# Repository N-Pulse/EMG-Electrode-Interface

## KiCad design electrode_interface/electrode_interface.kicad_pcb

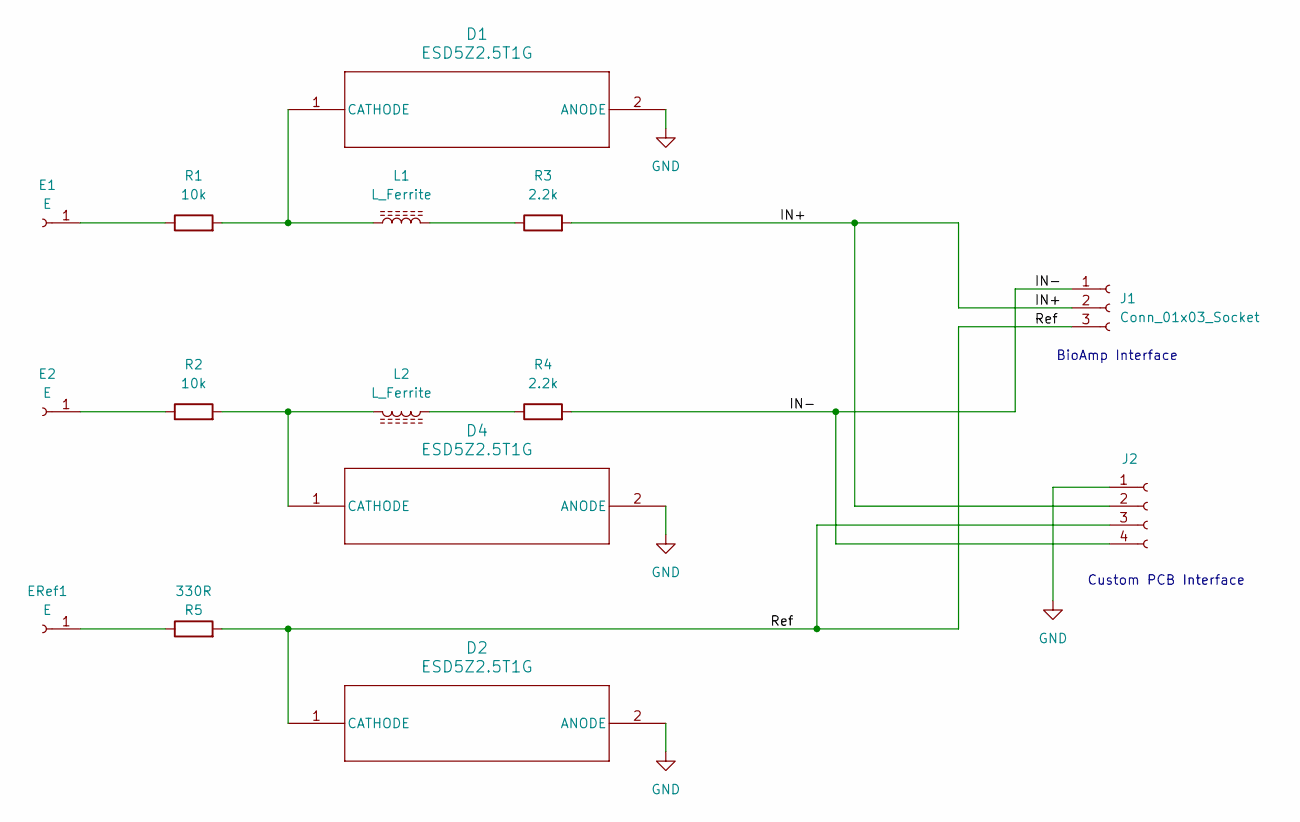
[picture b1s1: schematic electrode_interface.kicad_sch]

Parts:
D1, D2, D4: ESD5Z2.5T1G; SOD-523_0P9X1P3_ONS
E1, E2: E; ElectrodeHolder
ERef1: E; ElectrodeHolder
J1: Conn_01x03_Socket; PinHeader_1x03_P2.54mm_Vertical
J2: Conn_01x04_Socket; PinSocket_2x02_P2.54mm_Vertical
L1, L2: L_Ferrite; IND_BLM15_1P05X0P55X0P55_MUR
R1, R2: 10k; R_0402_1005Metric
R3, R4: 2.2k; R_0402_1005Metric
R5: 330R; R_0402_1005Metric

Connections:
/IN+: J1.2, J2.2, R3.2
/IN-: J1.1, J2.4, R4.2
/Ref: D2.1 (CATHODE), J1.3, J2.3, R5.2
GND: D1.2 (ANODE), D2.2 (ANODE), D4.2 (ANODE), J2.1
unnamed: D1.1 (CATHODE), L1.1, R1.2
unnamed: D4.1 (CATHODE), L2.2, R2.2
unnamed: E1.1, R1.1
unnamed: E2.1, R2.1
unnamed: ERef1.1, R5.1
unnamed: L1.2, R3.1
unnamed: L2.1, R4.1

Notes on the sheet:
BioAmp Interface
Custom PCB Interface

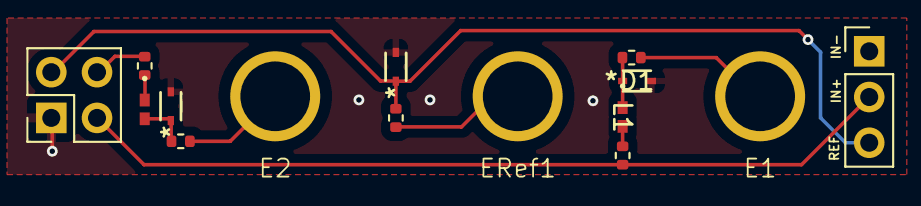
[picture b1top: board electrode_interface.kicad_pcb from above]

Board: 2 copper layers, 15 parts (0 on the bottom side), 11 nets.

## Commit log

2025-03-26 add license
2025-04-30 increase copper contour for electrode and add bioamp interface
